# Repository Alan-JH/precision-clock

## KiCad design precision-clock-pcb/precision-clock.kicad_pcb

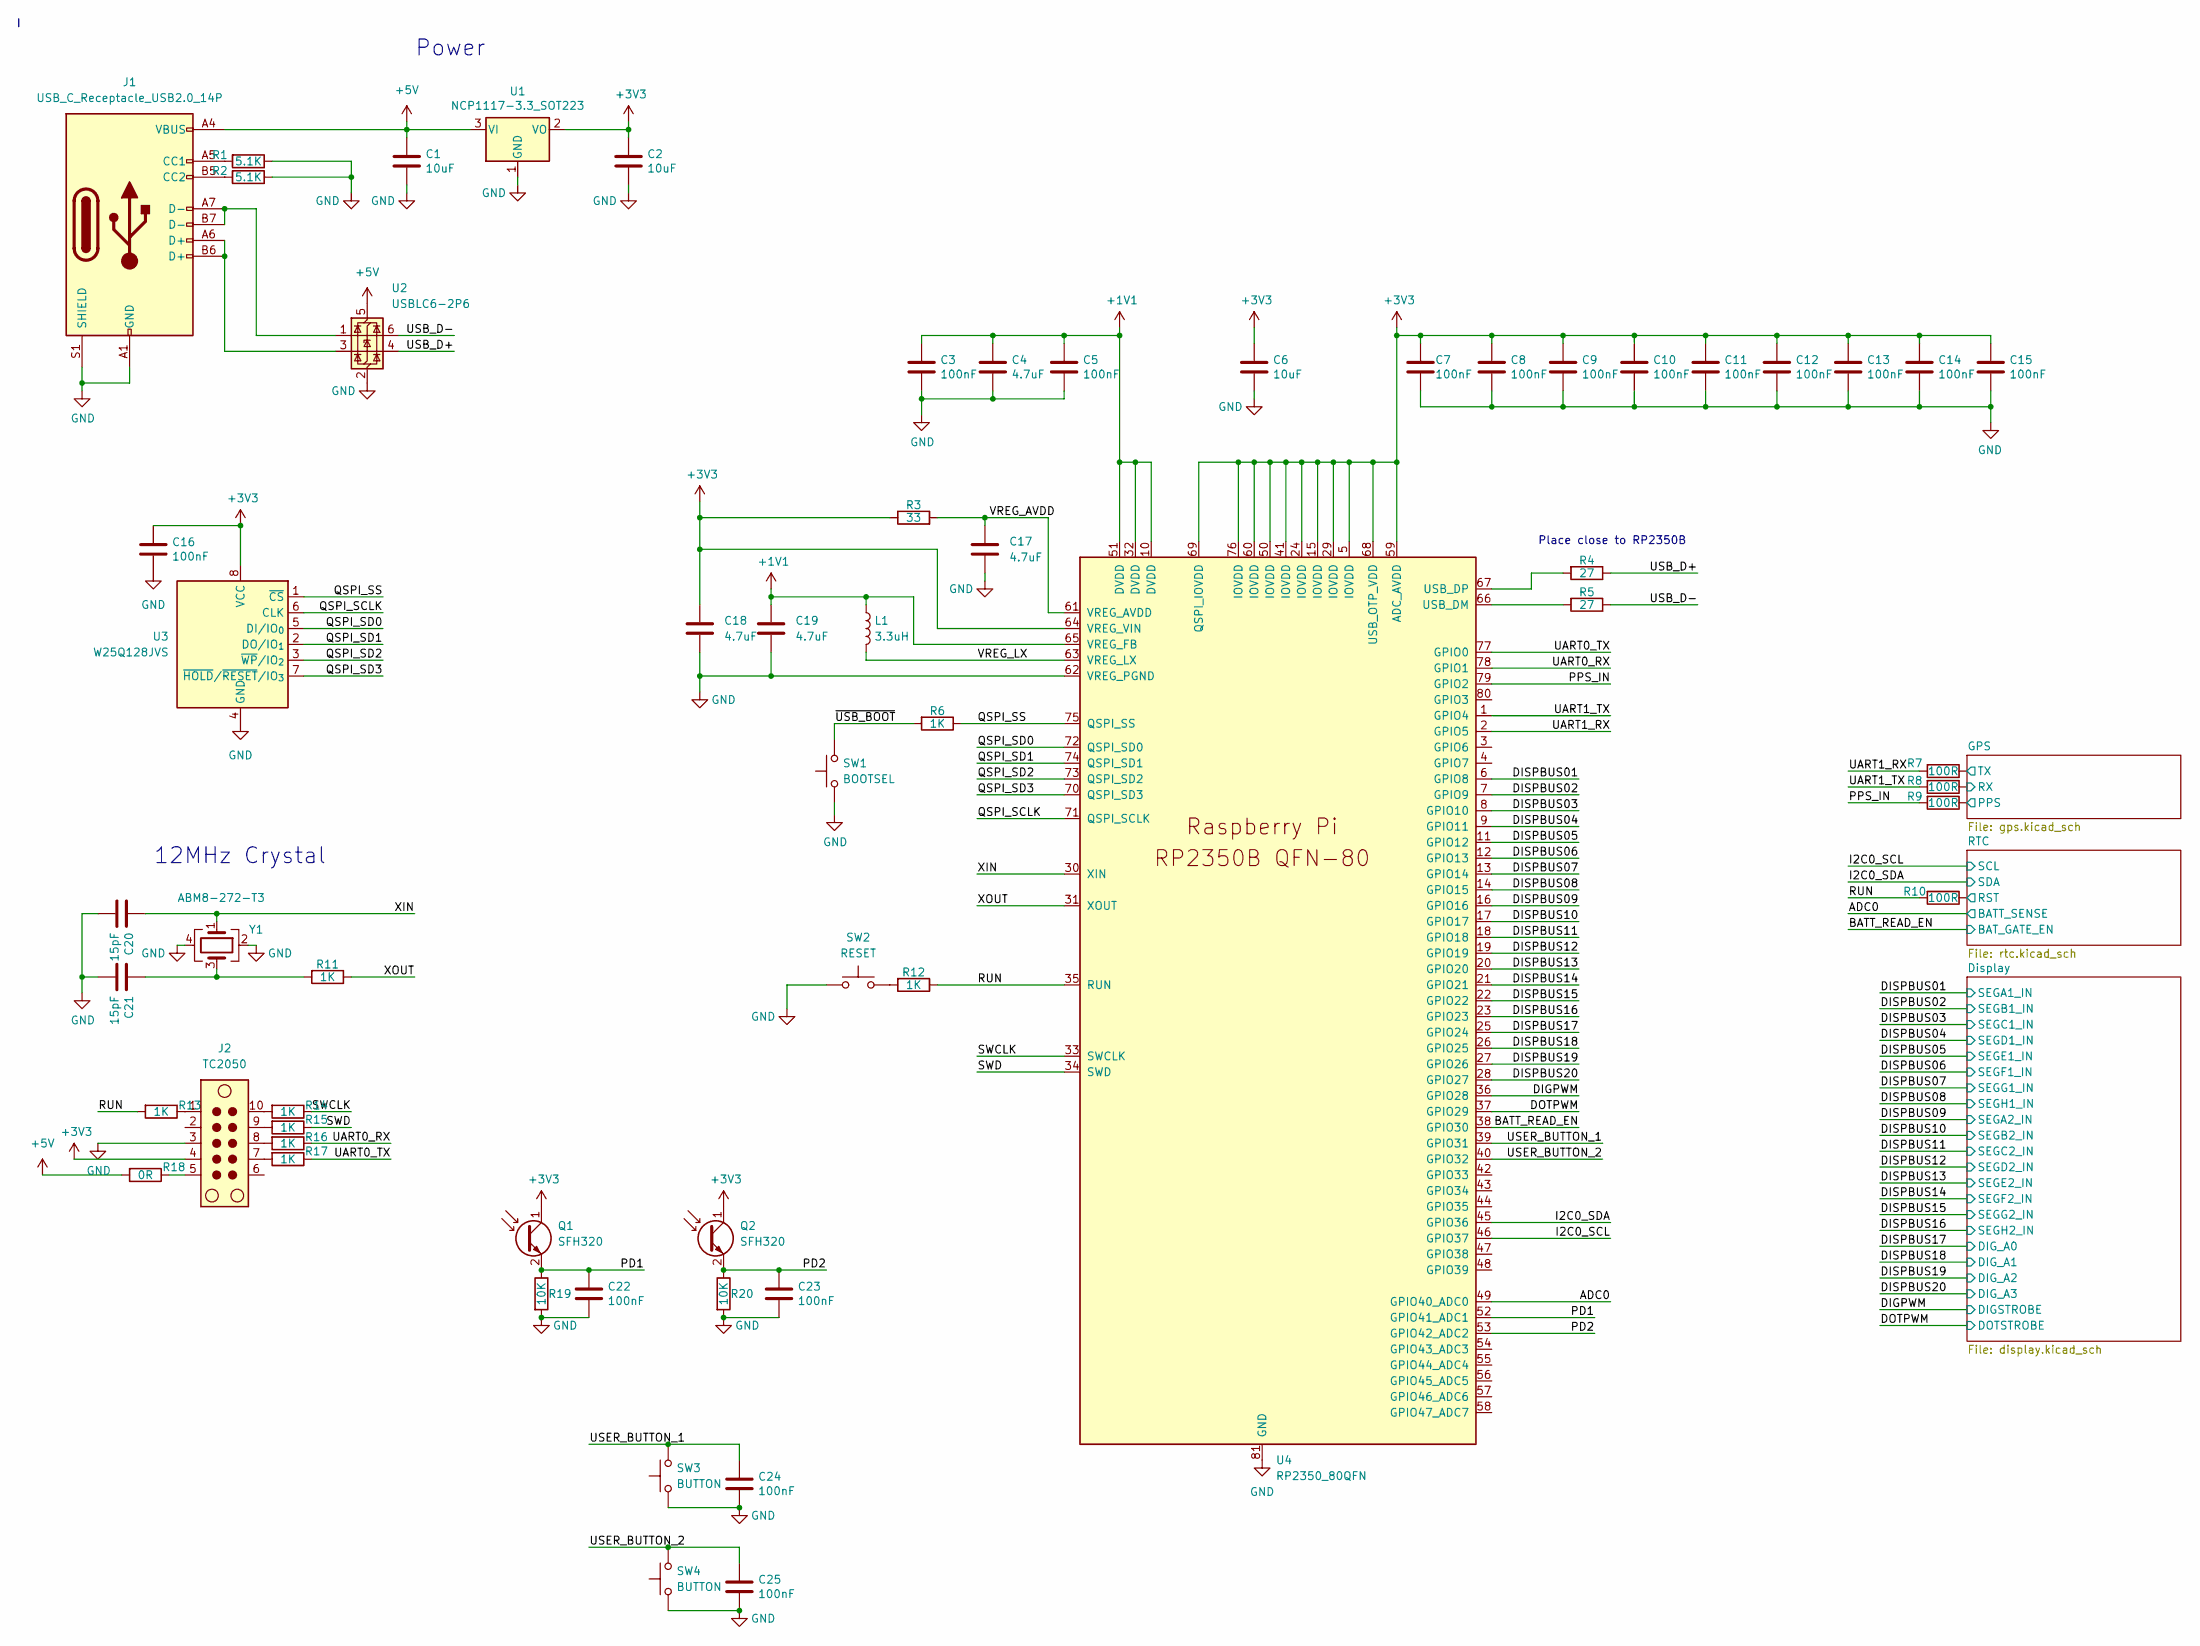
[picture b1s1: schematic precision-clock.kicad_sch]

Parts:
C1, C2, C6: 10uF; C_0805_2012Metric; MFR PN CL21B106KPQNNNE; JLCPCB PN C32635
C3, C5, C7, C8, C9, C10, C11, C12, C13, C14, C15, C16, C22, C23, C24, C25: 100nF; C_0402_1005Metric; MFR PN GRM155R71E104KE14D; JLCPCB PN C77014
C4, C17: 4.7uF; C_0402_1005Metric; MFR PN GRM155R61A475KEAAD; JLCPCB PN C77004
C18, C19: 4.7uF; C_0402_1005Metric_small_pads; MFR PN GRM155R61A475KEAAD; JLCPCB PN C77004
C20, C21: 15pF; C_0402_1005Metric; MFR PN CGA2B2C0G1H150JT0Y0F; JLCPCB PN C338103
J1: USB_C_Receptacle_USB2.0_14P; USB_C_Receptacle_G-Switch_GT-USB-7010ASV; MFR PN GT-USB-7010ASV; JLCPCB PN C2988369
J2: TC2050; Tag-Connect_TC2050-IDC-FP_2x05_P1.27mm_Vertical
L1: 3.3uH; L_pol_2016; MFR PN AOTA-B201610S3R3-101-T; JLCPCB PN C42411119
Q1, Q2: SFH320; LED_PLCC-2_3.4x3.0mm_KA; MFR PN SFH 320; JLCPCB PN C2900269
R1, R2: 5.1K; R_0402_1005Metric; MFR PN RC0402FR-075K1L; JLCPCB PN C105872
R3: 33; R_0402_1005Metric; MFR PN RC0402FR-0733RL; JLCPCB PN C138002
R4, R5: 27; R_0402_1005Metric; MFR PN RC0402FR-0727RL; JLCPCB PN C138021
R6, R11, R12, R13, R14, R15, R16, R17: 1K; R_0402_1005Metric; MFR PN RC0402FR-071KL; JLCPCB PN C106235
R7, R8, R9, R10: 100R; R_0402_1005Metric; MFR PN RC0402FR-07100RL; JLCPCB PN C106232
R18: 0R; R_0402_1005Metric; MFR PN RC0402FR-070RL; JLCPCB PN C106231
R19, R20: 10K; R_0402_1005Metric; MFR PN RC0402FR-0710KL; JLCPCB PN C60490
SW1: BOOTSEL; SW_SPST_PTS647_Sx38; MFR PN PTS647SM38SMTR2LFS; JLCPCB PN C2689502
SW2: RESET; SW_SPST_PTS647_Sx38; MFR PN PTS647SM38SMTR2LFS; JLCPCB PN C2689502
SW3, SW4: BUTTON; SW_SPST_PTS647_Sx38; MFR PN PTS647SM38SMTR2LFS; JLCPCB PN C2689502
U1: NCP1117-3.3_SOT223; SOT-223-3_TabPin2; MFR PN LM1117MPX-3.3/NOPB; JLCPCB PN C9662
U2: USBLC6-2P6; SOT-666; MFR PN USBLC6-2P6; JLCPCB PN C15999
U3: W25Q128JVS; SOIC-8_5.3x5.3mm_P1.27mm; MFR PN W25Q128JVSIQ; JLCPCB PN C97521
U4: RP2350_80QFN; RP2350-QFN-80-1EP_10x10_P0.4mm_EP3.4x3.4mm_ThermalVias; MFR PN RP2350B; JLCPCB PN C42415655
Y1: ABM8-272-T3; Crystal_SMD_3225-4Pin_3.2x2.5mm; MFR PN ABM8-272-T3; JLCPCB PN C20625731

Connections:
+1V1: C3.1, C4.1, C5.1, C19.1, L1.1, U4.10 (DVDD), U4.32 (DVDD), U4.51 (DVDD), U4.65 (VREG_FB)
+3V3: C2.1, C6.1, C7.1, C8.1, C9.1, C10.1, C11.1, C12.1, C13.1, C14.1, C15.1, C16.1, C18.1, J2.4, Q1.1 (C), Q2.1 (C), R3.1, U1.2 (VO), U3.8 (VCC), U4.5 (IOVDD), U4.15 (IOVDD), U4.24 (IOVDD), U4.29 (IOVDD), U4.41 (IOVDD), U4.50 (IOVDD), U4.59 (ADC_AVDD), U4.60 (IOVDD), U4.64 (VREG_VIN), U4.68 (USB_OTP_VDD), U4.69 (QSPI_IOVDD), U4.76 (IOVDD); also elsewhere on the board
+5V: C1.1, J1.A4 (VBUS), J1.A9 (VBUS), J1.B4 (VBUS), J1.B9 (VBUS), R18.2, U1.3 (VI), U2.5 (VBUS); also elsewhere on the board
/ADC0: U4.49 (GPIO40_ADC0); also elsewhere on the board
/BATT_READ_EN: U4.38 (GPIO30); also elsewhere on the board
/DIGPWM: U4.36 (GPIO28); also elsewhere on the board
/DISPBUS01: U4.6 (GPIO8); also elsewhere on the board
/DISPBUS02: U4.7 (GPIO9); also elsewhere on the board
/DISPBUS03: U4.8 (GPIO10); also elsewhere on the board
/DISPBUS04: U4.9 (GPIO11); also elsewhere on the board
/DISPBUS05: U4.11 (GPIO12); also elsewhere on the board
/DISPBUS06: U4.12 (GPIO13); also elsewhere on the board
/DISPBUS07: U4.13 (GPIO14); also elsewhere on the board
/DISPBUS08: U4.14 (GPIO15); also elsewhere on the board
/DISPBUS09: U4.16 (GPIO16); also elsewhere on the board
/DISPBUS10: U4.17 (GPIO17); also elsewhere on the board
/DISPBUS11: U4.18 (GPIO18); also elsewhere on the board
/DISPBUS12: U4.19 (GPIO19); also elsewhere on the board
/DISPBUS13: U4.20 (GPIO20); also elsewhere on the board
/DISPBUS14: U4.21 (GPIO21); also elsewhere on the board
/DISPBUS15: U4.22 (GPIO22); also elsewhere on the board
/DISPBUS16: U4.23 (GPIO23); also elsewhere on the board
/DISPBUS17: U4.25 (GPIO24); also elsewhere on the board
/DISPBUS18: U4.26 (GPIO25); also elsewhere on the board
/DISPBUS19: U4.27 (GPIO26); also elsewhere on the board
/DISPBUS20: U4.28 (GPIO27); also elsewhere on the board
/DOTPWM: U4.37 (GPIO29); also elsewhere on the board
/GPS/PPS: R9.1; also elsewhere on the board
/GPS/RX: R8.1; also elsewhere on the board
/GPS/TX: R7.1; also elsewhere on the board
/I2C0_SCL: U4.46 (GPIO37); also elsewhere on the board
/I2C0_SDA: U4.45 (GPIO36); also elsewhere on the board
/PD1: C22.1, Q1.2 (E), R19.1, U4.52 (GPIO41_ADC1)
/PD2: C23.1, Q2.2 (E), R20.1, U4.53 (GPIO42_ADC2)
/PPS_IN: R9.2, U4.79 (GPIO2)
/QSPI_SCLK: U3.6 (CLK), U4.71 (QSPI_SCLK)
/QSPI_SD0: U3.5 (DI/IO_{0}), U4.72 (QSPI_SD0)
/QSPI_SD1: U3.2 (DO/IO_{1}), U4.74 (QSPI_SD1)
/QSPI_SD2: U3.3 (~WP/IO_{2}), U4.73 (QSPI_SD2)
/QSPI_SD3: U3.7 (~HOLD/~RESET/IO_{3}), U4.70 (QSPI_SD3)
/QSPI_SS: R6.1, U3.1 (~CS), U4.75 (QSPI_SS)
/RTC/RST: R10.1; also elsewhere on the board
/RUN: R10.2, R12.1, R13.2, U4.35 (RUN)
/SWCLK: R14.1, U4.33 (SWCLK)
/SWD: R15.1, U4.34 (SWD)
/UART0_RX: R16.1, U4.78 (GPIO1)
/UART0_TX: R17.1, U4.77 (GPIO0)
/UART1_RX: R7.2, U4.2 (GPIO5)
/UART1_TX: R8.2, U4.1 (GPIO4)
/USB_D+: R4.1, U2.4 (I/O2)
/USB_D-: R5.1, U2.6 (I/O1)
/USER_BUTTON_1: C24.1, SW3.2, U4.39 (GPIO31)
/USER_BUTTON_2: C25.1, SW4.2, U4.40 (GPIO32)
/VREG_AVDD: C17.1, R3.2, U4.61 (VREG_AVDD)
/VREG_LX: L1.2, U4.63 (VREG_LX)
/XIN: C20.1, U4.30 (XIN), Y1.1
/XOUT: R11.1, U4.31 (XOUT)
/~USB_BOOT: R6.2, SW1.2
GND: C1.2, C2.2, C3.2, C4.2, C5.2, C6.2, C7.2, C8.2, C9.2, C10.2, C11.2, C12.2, C13.2, C14.2, C15.2, C16.2, C17.2, C18.2, C19.2, C20.2, C21.2, C22.2, C23.2, C24.2, C25.2, J1.A1 (GND), J1.A12 (GND), J1.B1 (GND), J1.B12 (GND), J1.S1 (SHIELD), J2.3, R1.1, R2.1, R19.2, R20.2, SW1.1, SW2.1, SW3.1, SW4.1, U1.1 (GND), U2.2 (GND), U3.4 (GND), U4.62 (VREG_PGND), U4.81 (GND), Y1.2, Y1.4; also elsewhere on the board
unnamed: C21.1, R11.2, Y1.3
unnamed: J1.A5 (CC1), R1.2
unnamed: J1.B5 (CC2), R2.2
unnamed: J1.A6 (D+), J1.B6 (D+), U2.3 (I/O2)
unnamed: J1.A7 (D-), J1.B7 (D-), U2.1 (I/O1)
unnamed: J2.1, R13.1
unnamed: J2.5, R18.1
unnamed: J2.7, R17.2
unnamed: J2.8, R16.2
unnamed: J2.9, R15.2
unnamed: J2.10, R14.2
unnamed: R12.2, SW2.2
unnamed: R5.2, U4.66 (USB_DM)
unnamed: R4.2, U4.67 (USB_DP)

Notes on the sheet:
12MHz Crystal
Place close to RP2350B
Power

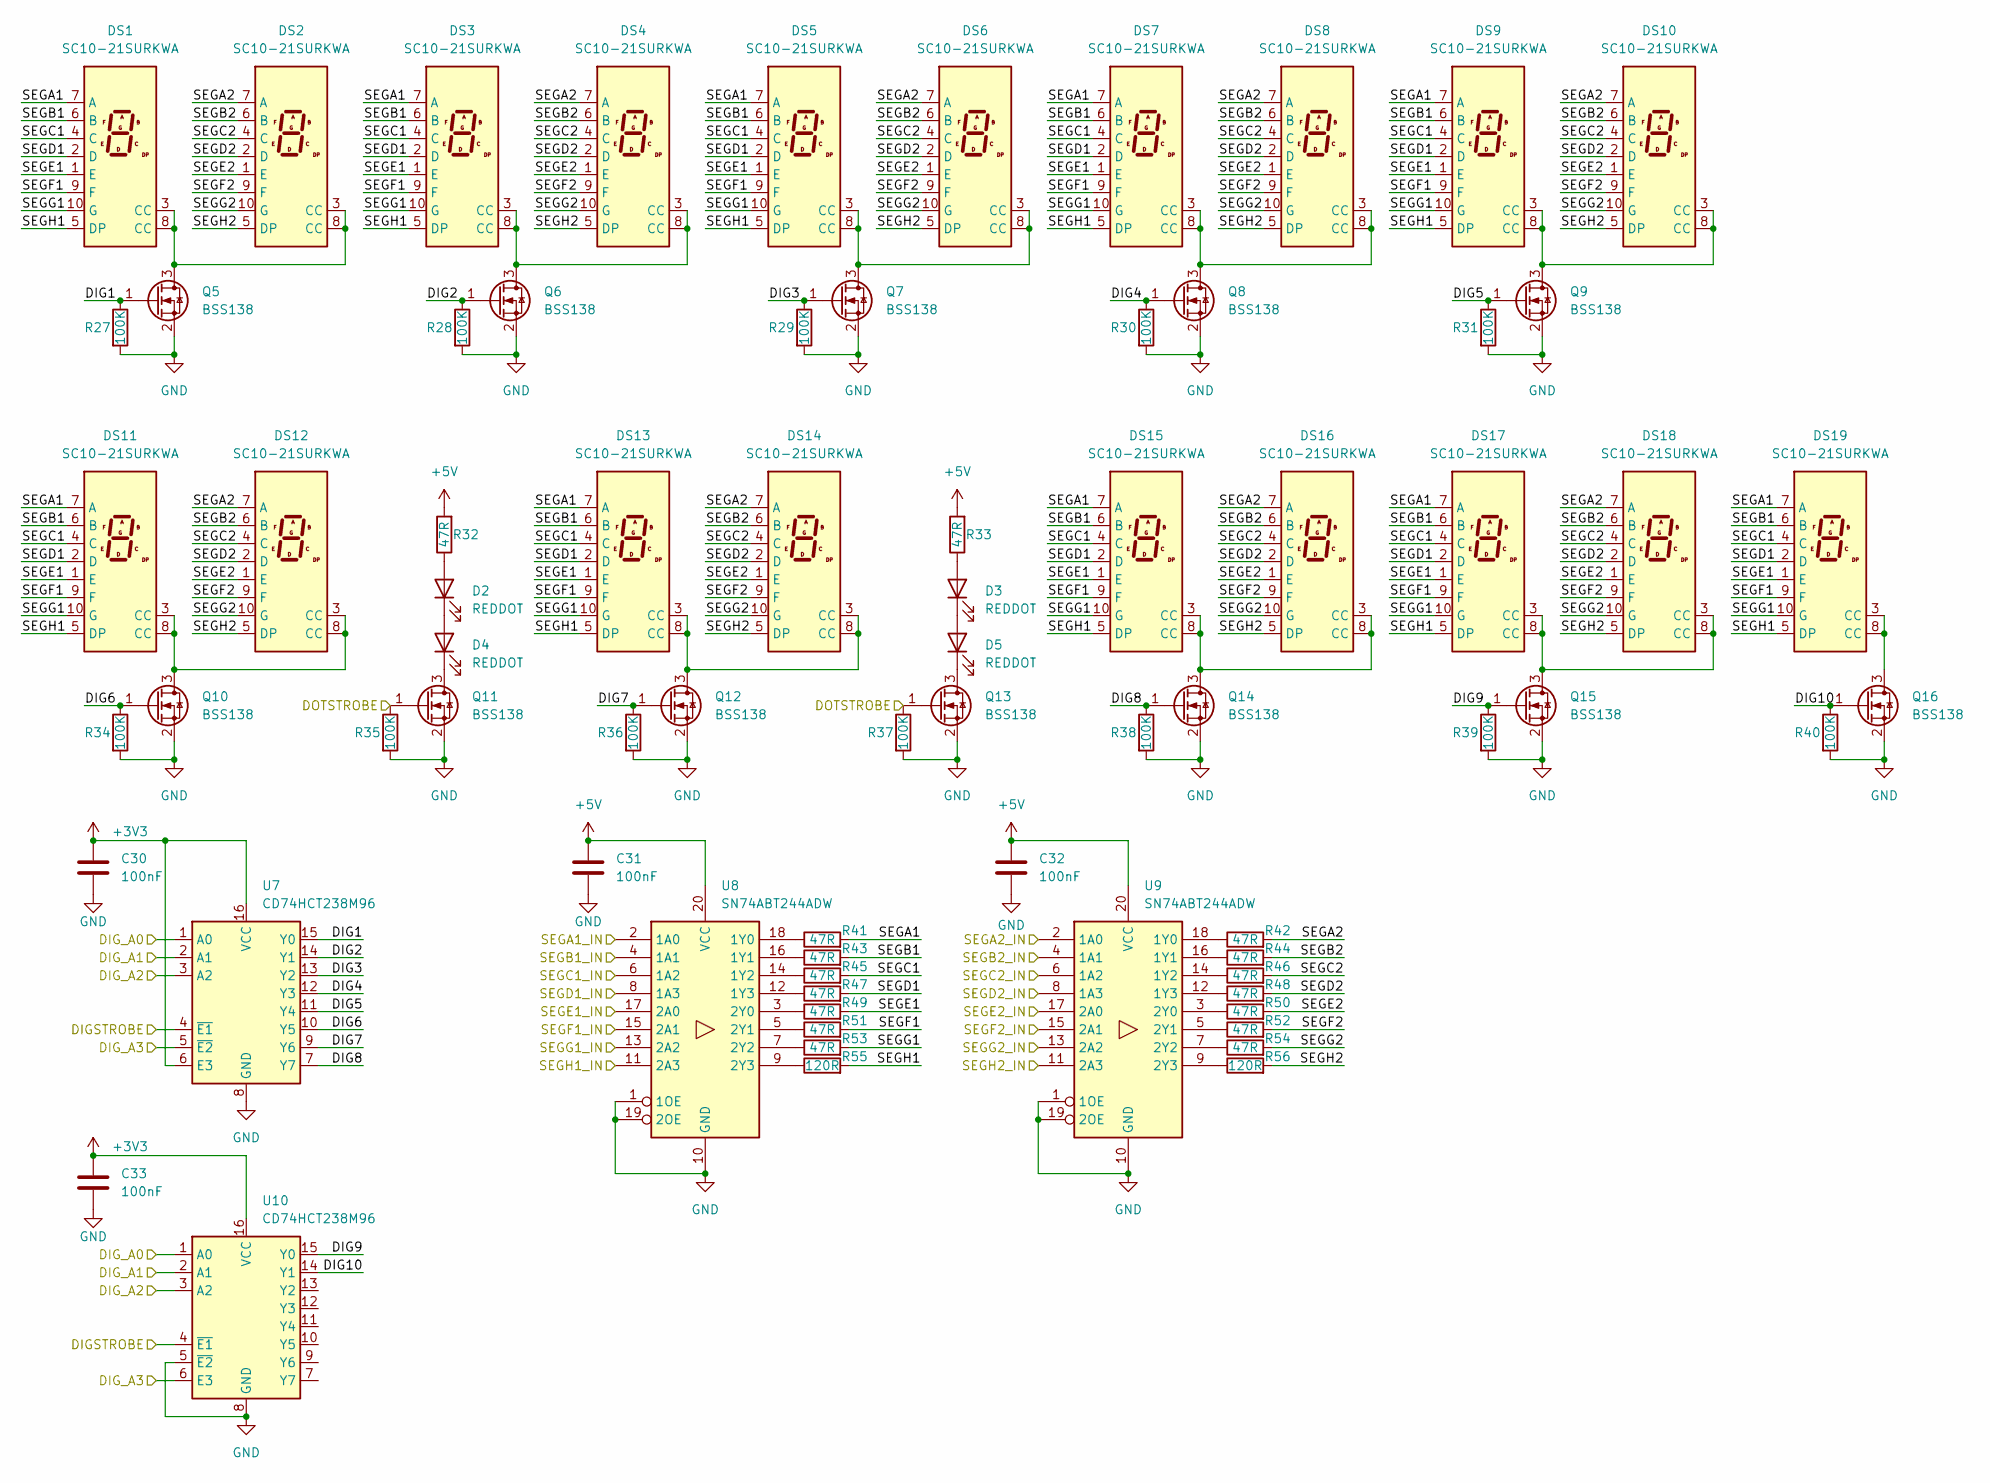
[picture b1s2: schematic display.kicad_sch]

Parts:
C30, C31, C32, C33: 100nF; C_0402_1005Metric; MFR PN GRM155R71E104KE14D; JLCPCB PN C77014
D2, D3, D4, D5: REDDOT; LED_D3.0mm; MFR PN 204-10SURD/S530-A3-L; JLCPCB PN C99771
DS1, DS2, DS3, DS4, DS5, DS6, DS7, DS8, DS9, DS10, DS11, DS12, DS13, DS14, DS15, DS16, DS17, DS18, DS19: SC10-21SURKWA; MFR PN SC10-21SURKWA; JLCPCB PN C6472270
Q5, Q6, Q7, Q8, Q9, Q10, Q11, Q12, Q13, Q14, Q15, Q16: BSS138; SOT-23; MFR PN BSS138; JLCPCB PN C52895
R27, R28, R29, R30, R31, R34, R35, R36, R37, R38, R39, R40: 100K; R_0402_1005Metric; MFR PN RC0402FR-07100KL; JLCPCB PN C60491
R32, R33, R41, R42, R43, R44, R45, R46, R47, R48, R49, R50, R51, R52, R53, R54: 47R; R_0402_1005Metric; MFR PN RC0402FR-0747RL; JLCPCB PN C137973
R55, R56: 120R; R_0402_1005Metric; MFR PN RC0402FR-07120RL; JLCPCB PN C114758
U7, U10: CD74HCT238M96; SOIC-16_3.9x9.9mm_P1.27mm; MFR PN CD74HCT238M96; JLCPCB PN C553161
U8, U9: SN74ABT244ADW; SOIC-20W_7.5x12.8mm_P1.27mm; MFR PN SN74ABT244ADWR; JLCPCB PN C2675811

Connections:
+3V3: C30.1, C33.1, U7.6 (E3), U7.16 (VCC), U10.16 (VCC); also elsewhere on the board
+5V: C31.1, C32.1, R32.2, R33.2, U8.20 (VCC), U9.20 (VCC); also elsewhere on the board
/DIGPWM: U7.4 (~E1), U10.4 (~E1); also elsewhere on the board
/DISPBUS01: U8.2 (1A0); also elsewhere on the board
/DISPBUS02: U8.4 (1A1); also elsewhere on the board
/DISPBUS03: U8.6 (1A2); also elsewhere on the board
/DISPBUS04: U8.8 (1A3); also elsewhere on the board
/DISPBUS05: U8.17 (2A0); also elsewhere on the board
/DISPBUS06: U8.15 (2A1); also elsewhere on the board
/DISPBUS07: U8.13 (2A2); also elsewhere on the board
/DISPBUS08: U8.11 (2A3); also elsewhere on the board
/DISPBUS09: U9.2 (1A0); also elsewhere on the board
/DISPBUS10: U9.4 (1A1); also elsewhere on the board
/DISPBUS11: U9.6 (1A2); also elsewhere on the board
/DISPBUS12: U9.8 (1A3); also elsewhere on the board
/DISPBUS13: U9.17 (2A0); also elsewhere on the board
/DISPBUS14: U9.15 (2A1); also elsewhere on the board
/DISPBUS15: U9.13 (2A2); also elsewhere on the board
/DISPBUS16: U9.11 (2A3); also elsewhere on the board
/DISPBUS17: U7.1 (A0), U10.1 (A0); also elsewhere on the board
/DISPBUS18: U7.2 (A1), U10.2 (A1); also elsewhere on the board
/DISPBUS19: U7.3 (A2), U10.3 (A2); also elsewhere on the board
/DISPBUS20: U7.5 (~E2), U10.6 (E3); also elsewhere on the board
/DOTPWM: Q11.1 (G), Q13.1 (G), R35.1, R37.1; also elsewhere on the board
/Display/DIG1: Q5.1 (G), R27.1, U7.15 (Y0)
/Display/DIG2: Q6.1 (G), R28.1, U7.14 (Y1)
/Display/DIG3: Q7.1 (G), R29.1, U7.13 (Y2)
/Display/DIG4: Q8.1 (G), R30.1, U7.12 (Y3)
/Display/DIG5: Q9.1 (G), R31.1, U7.11 (Y4)
/Display/DIG6: Q10.1 (G), R34.1, U7.10 (Y5)
/Display/DIG7: Q12.1 (G), R36.1, U7.9 (Y6)
/Display/DIG8: Q14.1 (G), R38.1, U7.7 (Y7)
/Display/DIG9: Q15.1 (G), R39.1, U10.15 (Y0)
/Display/DIG10: Q16.1 (G), R40.1, U10.14 (Y1)
/Display/SEGA1: DS1.7 (A), DS3.7 (A), DS5.7 (A), DS7.7 (A), DS9.7 (A), DS11.7 (A), DS13.7 (A), DS15.7 (A), DS17.7 (A), DS19.7 (A), R41.2
/Display/SEGA2: DS2.7 (A), DS4.7 (A), DS6.7 (A), DS8.7 (A), DS10.7 (A), DS12.7 (A), DS14.7 (A), DS16.7 (A), DS18.7 (A), R42.2
/Display/SEGB1: DS1.6 (B), DS3.6 (B), DS5.6 (B), DS7.6 (B), DS9.6 (B), DS11.6 (B), DS13.6 (B), DS15.6 (B), DS17.6 (B), DS19.6 (B), R43.2
/Display/SEGB2: DS2.6 (B), DS4.6 (B), DS6.6 (B), DS8.6 (B), DS10.6 (B), DS12.6 (B), DS14.6 (B), DS16.6 (B), DS18.6 (B), R44.2
/Display/SEGC1: DS1.4 (C), DS3.4 (C), DS5.4 (C), DS7.4 (C), DS9.4 (C), DS11.4 (C), DS13.4 (C), DS15.4 (C), DS17.4 (C), DS19.4 (C), R45.2
/Display/SEGC2: DS2.4 (C), DS4.4 (C), DS6.4 (C), DS8.4 (C), DS10.4 (C), DS12.4 (C), DS14.4 (C), DS16.4 (C), DS18.4 (C), R46.2
/Display/SEGD1: DS1.2 (D), DS3.2 (D), DS5.2 (D), DS7.2 (D), DS9.2 (D), DS11.2 (D), DS13.2 (D), DS15.2 (D), DS17.2 (D), DS19.2 (D), R47.2
/Display/SEGD2: DS2.2 (D), DS4.2 (D), DS6.2 (D), DS8.2 (D), DS10.2 (D), DS12.2 (D), DS14.2 (D), DS16.2 (D), DS18.2 (D), R48.2
/Display/SEGE1: DS1.1 (E), DS3.1 (E), DS5.1 (E), DS7.1 (E), DS9.1 (E), DS11.1 (E), DS13.1 (E), DS15.1 (E), DS17.1 (E), DS19.1 (E), R49.2
/Display/SEGE2: DS2.1 (E), DS4.1 (E), DS6.1 (E), DS8.1 (E), DS10.1 (E), DS12.1 (E), DS14.1 (E), DS16.1 (E), DS18.1 (E), R50.2
/Display/SEGF1: DS1.9 (F), DS3.9 (F), DS5.9 (F), DS7.9 (F), DS9.9 (F), DS11.9 (F), DS13.9 (F), DS15.9 (F), DS17.9 (F), DS19.9 (F), R51.2
/Display/SEGF2: DS2.9 (F), DS4.9 (F), DS6.9 (F), DS8.9 (F), DS10.9 (F), DS12.9 (F), DS14.9 (F), DS16.9 (F), DS18.9 (F), R52.2
/Display/SEGG1: DS1.10 (G), DS3.10 (G), DS5.10 (G), DS7.10 (G), DS9.10 (G), DS11.10 (G), DS13.10 (G), DS15.10 (G), DS17.10 (G), DS19.10 (G), R53.2
/Display/SEGG2: DS2.10 (G), DS4.10 (G), DS6.10 (G), DS8.10 (G), DS10.10 (G), DS12.10 (G), DS14.10 (G), DS16.10 (G), DS18.10 (G), R54.2
/Display/SEGH1: DS1.5 (DP), DS3.5 (DP), DS5.5 (DP), DS7.5 (DP), DS9.5 (DP), DS11.5 (DP), DS13.5 (DP), DS15.5 (DP), DS17.5 (DP), DS19.5 (DP), R55.2
/Display/SEGH2: DS2.5 (DP), DS4.5 (DP), DS6.5 (DP), DS8.5 (DP), DS10.5 (DP), DS12.5 (DP), DS14.5 (DP), DS16.5 (DP), DS18.5 (DP), R56.2
GND: C30.2, C31.2, C32.2, C33.2, Q5.2 (S), Q6.2 (S), Q7.2 (S), Q8.2 (S), Q9.2 (S), Q10.2 (S), Q11.2 (S), Q12.2 (S), Q13.2 (S), Q14.2 (S), Q15.2 (S), Q16.2 (S), R27.2, R28.2, R29.2, R30.2, R31.2, R34.2, R35.2, R36.2, R37.2, R38.2, R39.2, R40.2, U7.8 (GND), U8.1 (1OE), U8.10 (GND), U8.19 (2OE), U9.1 (1OE), U9.10 (GND), U9.19 (2OE), U10.5 (~E2), U10.8 (GND); also elsewhere on the board
unnamed: D2.2 (A), R32.1
unnamed: D2.1 (K), D4.2 (A)
unnamed: D3.2 (A), R33.1
unnamed: D3.1 (K), D5.2 (A)
unnamed: D4.1 (K), Q11.3 (D)
unnamed: D5.1 (K), Q13.3 (D)
unnamed: DS1.3 (CC), DS1.8 (CC), DS2.3 (CC), DS2.8 (CC), Q5.3 (D)
unnamed: DS3.3 (CC), DS3.8 (CC), DS4.3 (CC), DS4.8 (CC), Q6.3 (D)
unnamed: DS5.3 (CC), DS5.8 (CC), DS6.3 (CC), DS6.8 (CC), Q7.3 (D)
unnamed: DS7.3 (CC), DS7.8 (CC), DS8.3 (CC), DS8.8 (CC), Q8.3 (D)
unnamed: DS9.3 (CC), DS9.8 (CC), DS10.3 (CC), DS10.8 (CC), Q9.3 (D)
unnamed: DS11.3 (CC), DS11.8 (CC), DS12.3 (CC), DS12.8 (CC), Q10.3 (D)
unnamed: DS13.3 (CC), DS13.8 (CC), DS14.3 (CC), DS14.8 (CC), Q12.3 (D)
unnamed: DS15.3 (CC), DS15.8 (CC), DS16.3 (CC), DS16.8 (CC), Q14.3 (D)
unnamed: DS17.3 (CC), DS17.8 (CC), DS18.3 (CC), DS18.8 (CC), Q15.3 (D)
unnamed: DS19.3 (CC), DS19.8 (CC), Q16.3 (D)
unnamed: R41.1, U8.18 (1Y0)
unnamed: R43.1, U8.16 (1Y1)
unnamed: R45.1, U8.14 (1Y2)
unnamed: R47.1, U8.12 (1Y3)
unnamed: R49.1, U8.3 (2Y0)
unnamed: R51.1, U8.5 (2Y1)
unnamed: R53.1, U8.7 (2Y2)
unnamed: R55.1, U8.9 (2Y3)
unnamed: R42.1, U9.18 (1Y0)
unnamed: R44.1, U9.16 (1Y1)
unnamed: R46.1, U9.14 (1Y2)
unnamed: R48.1, U9.12 (1Y3)
unnamed: R50.1, U9.3 (2Y0)
unnamed: R52.1, U9.5 (2Y1)
unnamed: R54.1, U9.7 (2Y2)
unnamed: R56.1, U9.9 (2Y3)

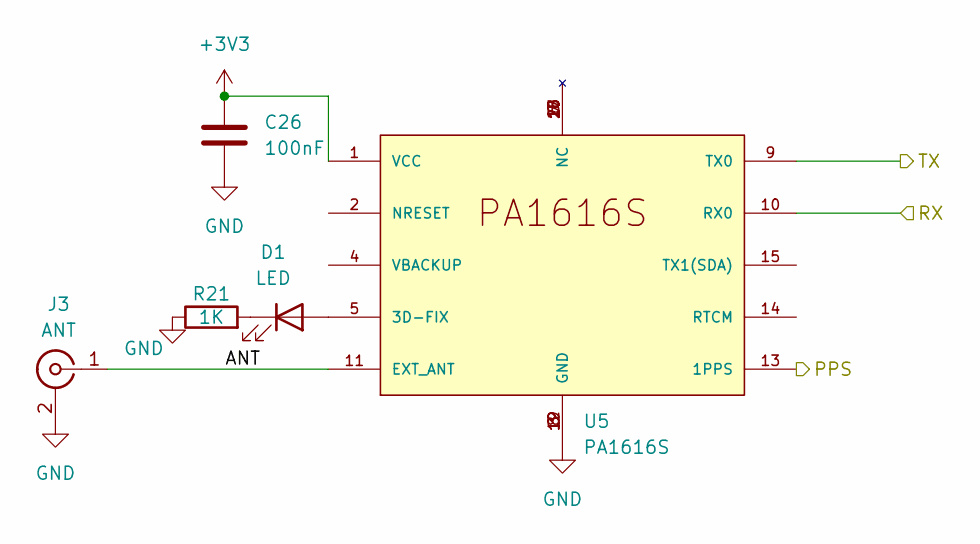
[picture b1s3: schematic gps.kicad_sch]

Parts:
C26: 100nF; C_0402_1005Metric
D1: LED; LED_0603_1608Metric
J3: ANT; MMCX_Molex_73415-1471_Vertical
R21: 1K; R_0402_1005Metric
U5: PA1616S

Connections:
+3V3: C26.1, U5.1 (VCC); also elsewhere on the board
/GPS/ANT: J3.1 (In), U5.11 (EXT_ANT)
/GPS/PPS: U5.13 (1PPS); also elsewhere on the board
/GPS/RX: U5.10 (RX0); also elsewhere on the board
/GPS/TX: U5.9 (TX0); also elsewhere on the board
GND: C26.2, J3.2 (Ext), R21.1, U5.3 (GND), U5.8 (GND), U5.12 (GND), U5.19 (GND); also elsewhere on the board
unnamed: D1.2 (A), U5.5 (3D-FIX)
unnamed: D1.1 (K), R21.2

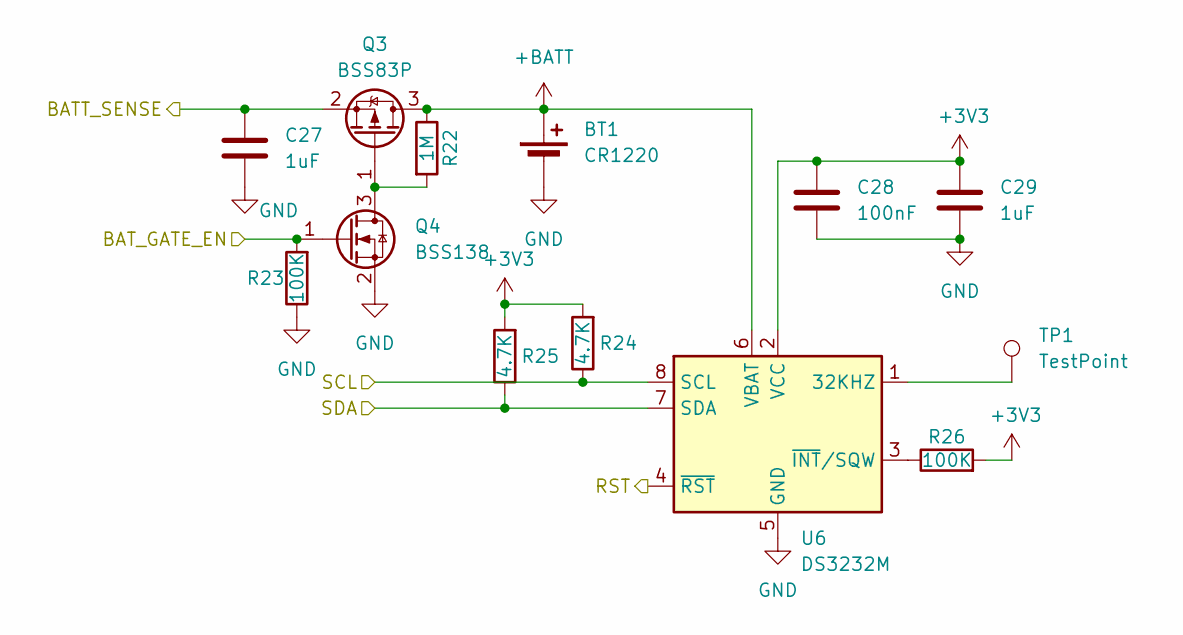
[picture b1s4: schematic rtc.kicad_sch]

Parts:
BT1: CR1220; BAT_2895
C27, C29: 1uF; C_0603_1608Metric
C28: 100nF; C_0402_1005Metric
Q3: BSS83P; SOT-23
Q4: BSS138; SOT-23
R22: 1M; R_0402_1005Metric
R23, R26: 100K; R_0402_1005Metric
R24, R25: 4.7K; R_0402_1005Metric
TP1: TestPoint; TestPoint_Pad_2.0x2.0mm
U6: DS3232M; SOIC-8_3.9x4.9mm_P1.27mm

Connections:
+3V3: C28.1, C29.1, R24.2, R25.2, R26.2, U6.2 (VCC); also elsewhere on the board
+BATT: BT1.1 (+), Q3.3 (D), R22.1, U6.6 (VBAT)
/ADC0: C27.1, Q3.2 (S); also elsewhere on the board
/BATT_READ_EN: Q4.1 (G), R23.2; also elsewhere on the board
/I2C0_SCL: R24.1, U6.8 (SCL); also elsewhere on the board
/I2C0_SDA: R25.1, U6.7 (SDA); also elsewhere on the board
/RTC/RST: U6.4 (~RST); also elsewhere on the board
GND: BT1.2 (-), C27.2, C28.2, C29.2, Q4.2 (S), R23.1, U6.5 (GND); also elsewhere on the board
unnamed: Q3.1 (G), Q4.3 (D), R22.2
unnamed: TP1.1, U6.1 (32KHZ)
unnamed: R26.1, U6.3 (~INT/SQW)

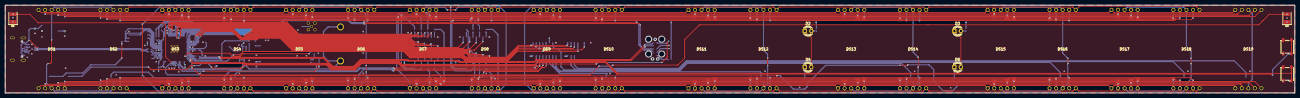
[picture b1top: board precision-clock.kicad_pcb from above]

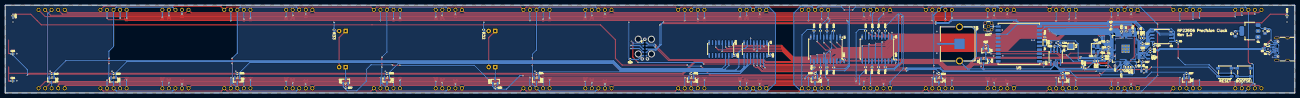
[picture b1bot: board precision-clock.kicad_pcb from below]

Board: 4 copper layers, 500.0 x 34.0 mm, 150 parts (123 on the bottom side), 138 nets.

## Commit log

2025-11-06 Revert "Initial commit"
    This reverts commit 37d97fef083f5c2f4647276c4944423df487484e.
2025-11-06 Revert "Revert "Initial commit""
    This reverts commit 25a4185e54c432d465cfb9da8a8ced92ea69207e.
2025-11-06 rename
2025-11-06 init pio stuff
2025-11-07 correct pio setup
2025-11-11 display work
2025-11-12 schematic work done
2025-11-13 gps code go brr
2025-11-13 display code
2025-11-14 ADC Backup Battery
2025-11-14 Formatting
2025-11-14 board work
2025-11-14 rtc functions
2025-11-15 Board Rev 1.0 Release
2025-11-18 BOM, CSV, and STEP exports
2025-11-18 fix bom and recompress gerbers
2025-11-20 integrate RTC functionality and PPS tuning capability
2025-11-20 come back here if you fuck up
2025-11-20 ts finally works
2025-11-21 work
2025-11-21 chatgpt lied about timers
2025-11-21 fix rtc jitter issue
2025-11-21 clean up gps a bit
2025-11-25 updating from GPS
2025-11-25 comment
2025-11-25 fix timers
